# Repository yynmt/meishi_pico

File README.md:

# meishi_pico

meishi using Raspberry Pi Pico

- [ビルドガイド](/docs/buildguide_jp.md)

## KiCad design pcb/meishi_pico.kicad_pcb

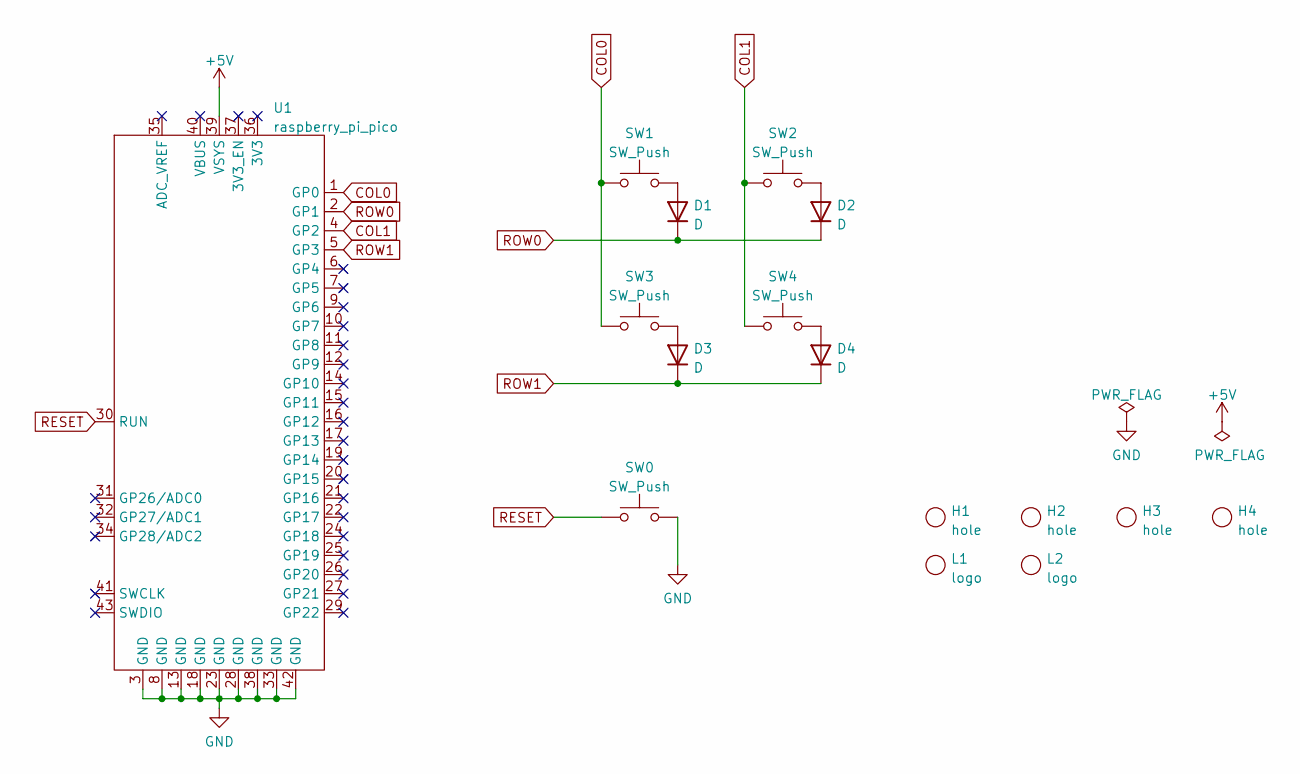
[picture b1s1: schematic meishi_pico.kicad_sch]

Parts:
D1, D2, D3, D4: D; diode
H1, H2, H3, H4: hole; hole_m2
L1: logo
L2: logo; logo_yynmt
SW0: SW_Push; switch_tact
SW1, SW2, SW3, SW4: SW_Push; switch_mx_kailh
U1: raspberry_pi_pico

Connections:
+5V: U1.39 (VSYS)
COL0: SW1.1, SW3.1, U1.1 (GP0)
COL1: SW2.1, SW4.1, U1.4 (GP2)
GND: SW0.2, U1.3 (GND), U1.8 (GND), U1.13 (GND), U1.18 (GND), U1.23 (GND), U1.28 (GND), U1.33 (GND), U1.38 (GND), U1.42 (GND)
unnamed: D1.2 (A), SW1.2
unnamed: D2.2 (A), SW2.2
unnamed: D3.2 (A), SW3.2
unnamed: D4.2 (A), SW4.2
RESET: SW0.1, U1.30 (RUN)
ROW0: D1.1 (K), D2.1 (K), U1.2 (GP1)
ROW1: D3.1 (K), D4.1 (K), U1.5 (GP3)

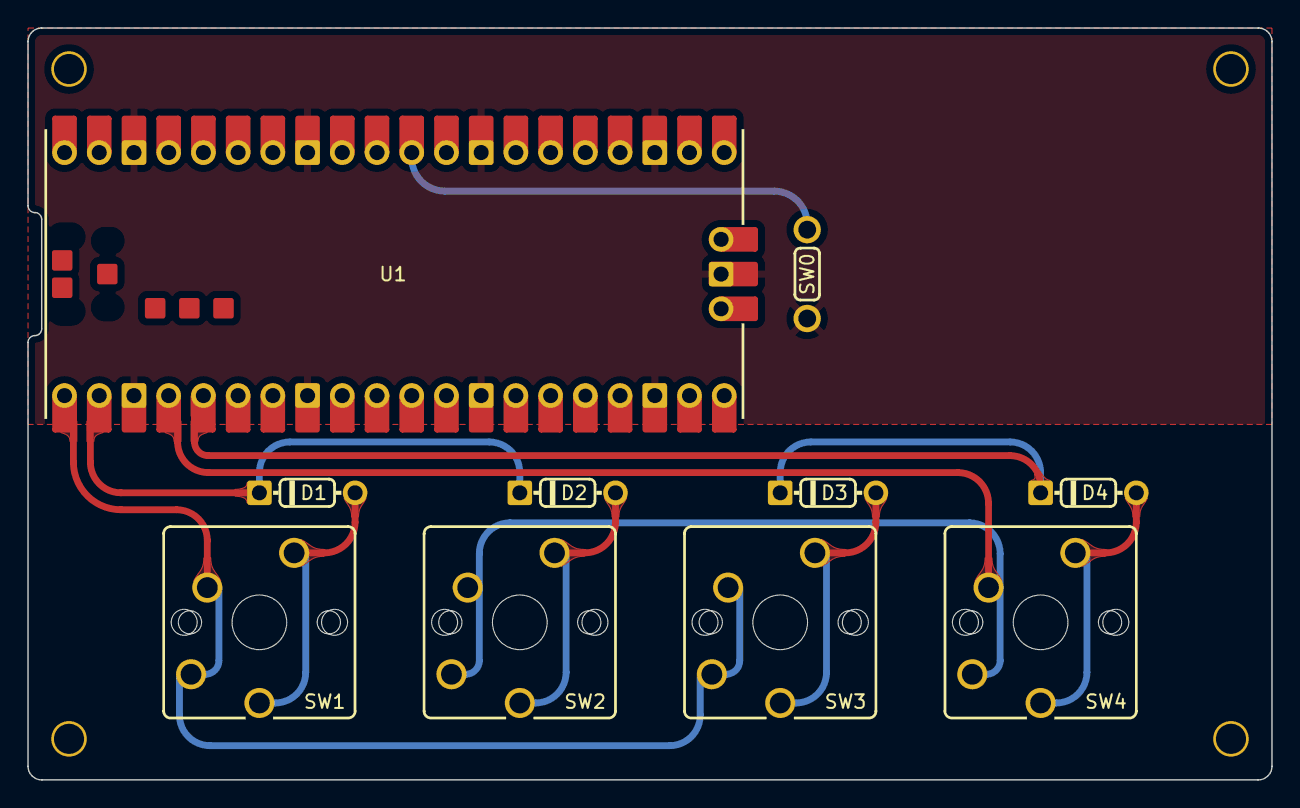
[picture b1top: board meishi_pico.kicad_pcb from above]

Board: 2 copper layers, 91.0 x 55.0 mm, 16 parts (1 on the bottom side), 10 nets.

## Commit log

2022-09-02 add pcb, initial commit
2022-09-04 Add main image
